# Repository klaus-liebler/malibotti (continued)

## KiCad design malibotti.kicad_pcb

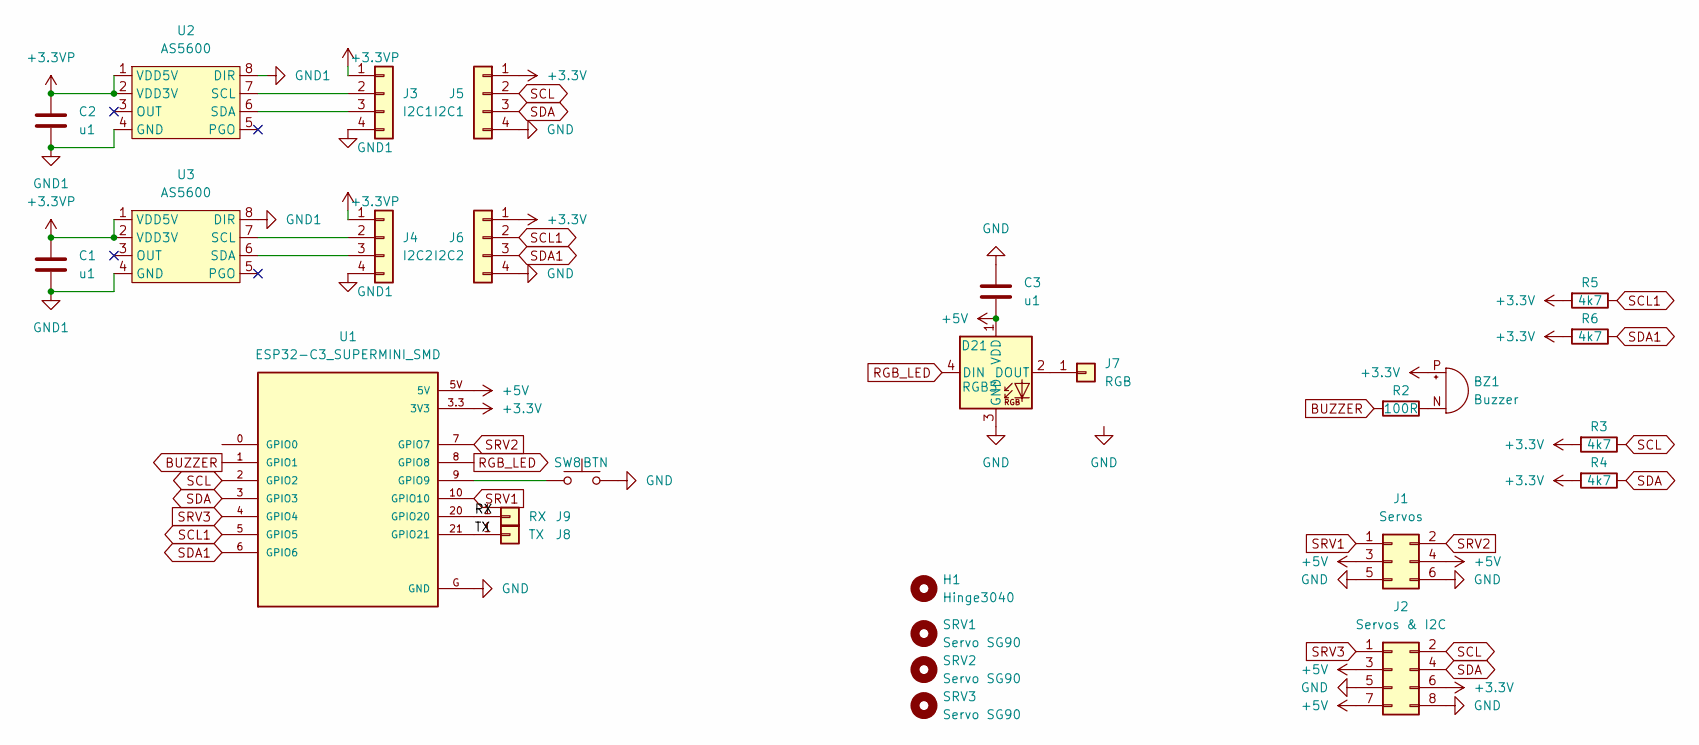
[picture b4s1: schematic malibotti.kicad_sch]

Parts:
BZ1: Buzzer; XDCR_CMT-7525-80-SMT-TR_handsolder
C1, C2, C3: u1; C_1206_3216Metric_Pad1.33x1.80mm_HandSolder
D21: RGB3; SK6812MINI-E_REV; MPN SK6812MINI-EA
H1: Hinge3040; Hinge_3040
J1: Servos; PinHeader_2x03_P2.54mm_Vertical_SMD
J2: Servos & I2C; PinHeader_2x04_P2.54mm_Vertical_SMD
J3: I2C1; PinHeader_1x04_P2.54mm_Vertical
J4: I2C2; PinHeader_1x04_P2.54mm_Vertical
J5: I2C1; PinSocket_1x04_P2.54mm_Vertical
J6: I2C2; PinSocket_1x04_P2.54mm_Vertical
J7: RGB; TestPoint_Pad_1.5x1.5mm
J8: TX; TestPoint_Pad_1.5x1.5mm
J9: RX; TestPoint_Pad_1.5x1.5mm
R2: 100R; R_1206_3216Metric_Pad1.30x1.75mm_HandSolder
R3, R4, R5, R6: 4k7; R_1206_3216Metric_Pad1.30x1.75mm_HandSolder
SRV1, SRV2: Servo SG90; SG90_PCB
SRV3: Servo SG90; SG90_vertical_PCB
SW8: BTN; SW_Push_1P1T_NO_6x6mm_H6.5mm_Reverse; MPN TS-1095E-A6B3-D2
U1: ESP32-C3_SUPERMINI_SMD; MODULE_ESP32-C3_SUPERMINI
U2, U3: AS5600; SOIC-8_3.9x4.9mm_P1.27mm_handsolder

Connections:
+3.3V: BZ1.P (+), J2.6, J5.1, J6.1, R3.2, R4.2, R5.2, R6.2, U1.3.3 (3V3)
+3.3VP: C1.1, C2.1, J3.1, J4.1, U2.1 (VDD5V), U2.2 (VDD3V), U3.1 (VDD5V), U3.2 (VDD3V)
+5V: C3.1, D21.1 (VDD), J1.3, J1.4, J2.3, J2.7, U1.5V
/RX: J9.1, U1.20 (GPIO20)
/TX: J8.1, U1.21 (GPIO21)
BUZZER: R2.2, U1.1 (GPIO1)
GND: C3.2, D21.3 (GND), J1.5, J1.6, J2.5, J2.8, J5.4, J6.4, SW8.2, U1.G (GND)
GND1: C1.2, C2.2, J3.4, J4.4, U2.4 (GND), U2.8 (DIR), U3.4 (GND), U3.8 (DIR)
unnamed: BZ1.N (-), R2.1
unnamed: D21.2 (DOUT), J7.1
unnamed: J3.2, U2.7 (SCL)
unnamed: J3.3, U2.6 (SDA)
unnamed: J4.2, U3.7 (SCL)
unnamed: J4.3, U3.6 (SDA)
unnamed: SW8.1, U1.9 (GPIO9)
RGB_LED: D21.4 (DIN), U1.8 (GPIO8)
SCL: J2.2, J5.2, R3.1, U1.2 (GPIO2)
SCL1: J6.2, R5.1, U1.5 (GPIO5)
SDA: J2.4, J5.3, R4.1, U1.3 (GPIO3)
SDA1: J6.3, R6.1, U1.6 (GPIO6)
SRV1: J1.1, U1.10 (GPIO10)
SRV2: J1.2, U1.7 (GPIO7)
SRV3: J2.1, U1.4 (GPIO4)

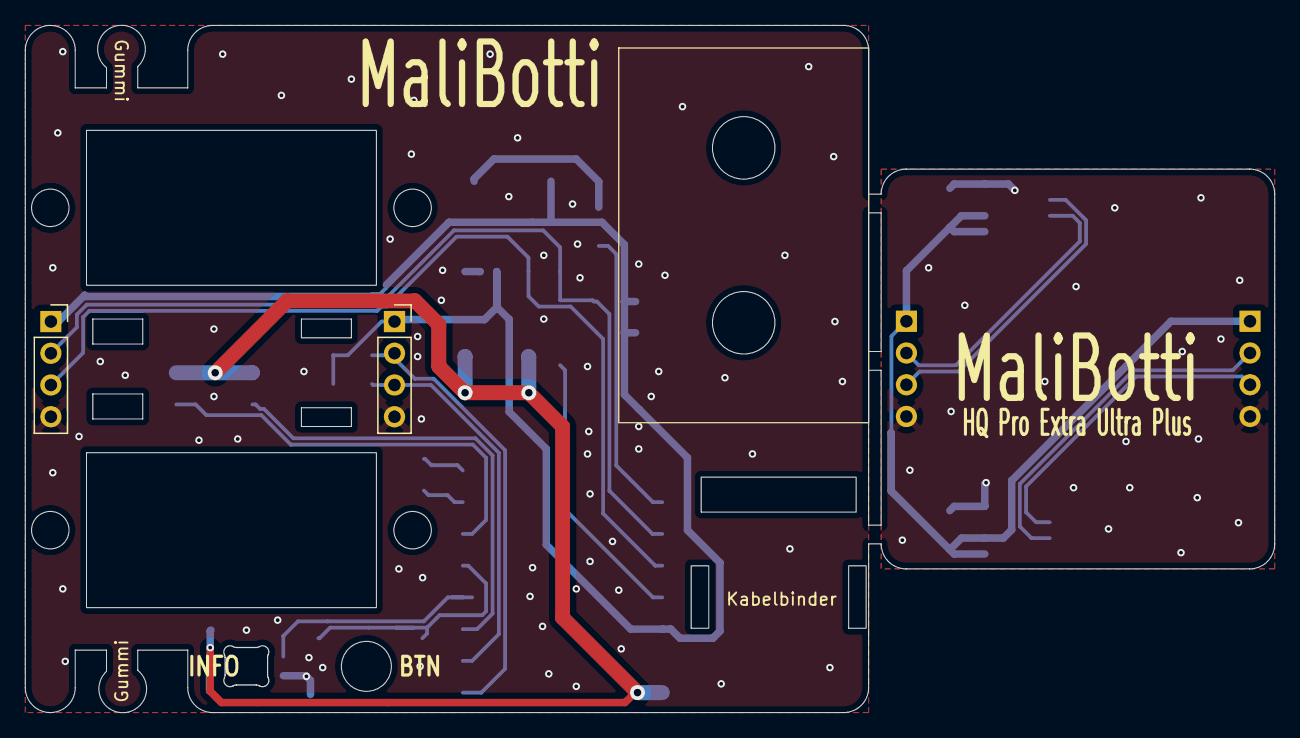
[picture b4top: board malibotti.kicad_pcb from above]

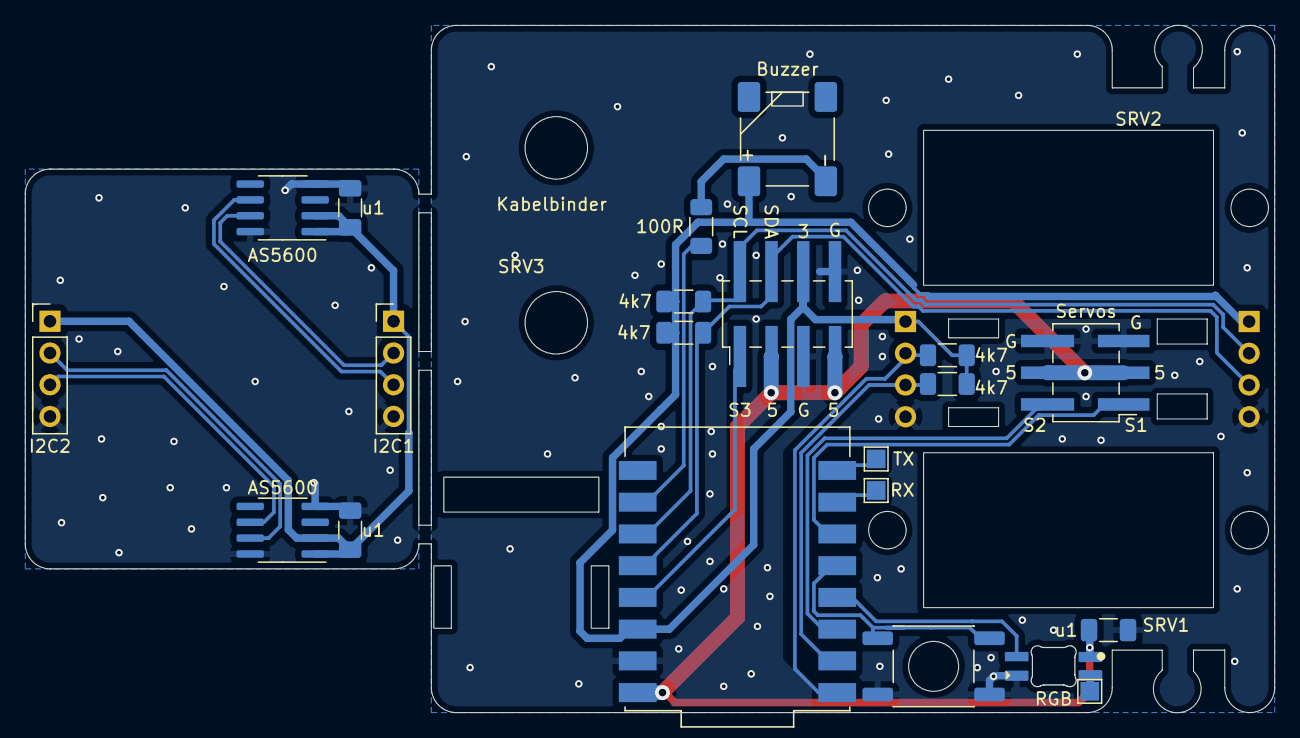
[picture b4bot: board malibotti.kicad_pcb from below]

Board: 2 copper layers, 100.0 x 55.0 mm, 27 parts (21 on the bottom side), 23 nets.

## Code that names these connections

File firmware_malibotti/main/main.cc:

#include <stdlib.h>
#include <stdio.h>
#include <string.h>
#include <errno.h>
#include <stdarg.h>
#include <fcntl.h>
#include <array>
#include <sys/types.h>
#include <unistd.h>

#include "sdkconfig.h"
#include "esp_log.h"
#include "esp_mac.h"
#include "esp_system.h"
#include "esp_vfs.h"
#include "freertos/FreeRTOS.h"
#include "freertos/task.h"
#include "rgbled.hh"
#include "esp_rom_gpio.h"

#include "hal/gpio_ll.h"

#include "driver/gpio.h"
#include "driver/uart.h"

#include "buzzer.hh"
#include "listener/echo_message_processor.hh"
#include "listener/rgb_message_processor.hh"
#include "listener/servo_message_processor.hh"
#include "listener/stepper_message_processor.hh"
#include "stepper_unipolar.hh"
#include "usb.hh"

constexpr const char MONITOR_LOG_TAG[] = "monitor";

namespace P
{
  constexpr gpio_num_t BUTTON{GPIO_NUM_0};
  constexpr gpio_num_t LIMIT_RIGHT{GPIO_NUM_6};
  constexpr gpio_num_t LIMIT_LEFT{GPIO_NUM_7};
  constexpr gpio_num_t RGB_LED{GPIO_NUM_11};
  constexpr gpio_num_t STEPPER1_PH1{GPIO_NUM_21};
  constexpr gpio_num_t STEPPER1_PH2{GPIO_NUM_47};
  constexpr gpio_num_t STEPPER1_PH3{GPIO_NUM_34};
  constexpr gpio_num_t STEPPER1_PH4{GPIO_NUM_35};
  constexpr gpio_num_t STEPPER2_PH1{GPIO_NUM_36};
  constexpr gpio_num_t STEPPER2_PH2{GPIO_NUM_48};
  constexpr gpio_num_t STEPPER2_PH3{GPIO_NUM_33};
  constexpr gpio_num_t STEPPER2_PH4{GPIO_NUM_26};
  constexpr gpio_num_t SERVO{GPIO_NUM_37};
  constexpr gpio_num_t BUZZER{GPIO_NUM_38};
  constexpr gpio_num_t SDA{GPIO_NUM_39};
  constexpr gpio_num_t SCL{GPIO_NUM_40};
}

namespace stepper_settings
{
  constexpr uint16_t STEPS_PER_REV = 2048;
  constexpr uint32_t MAX_RPM = 12;
  constexpr TickType_t TURN_PAUSE = pdMS_TO_TICKS(500);
  constexpr bool USE_HALF_STEP = false;
}

constexpr TickType_t CDC_LOG_WRITE_TIMEOUT_TICKS = pdMS_TO_TICKS(20);

/* Blink pattern
 * - 250 ms  : device not mounted
 * - 1000 ms : device mounted
 * - 2500 ms : device is suspended
 */
RGBLED::BlinkPattern NOT_MOUNTED(CRGB::Red, 250, CRGB::Black, 250);
RGBLED::BlinkPattern MOUNTED(CRGB::Green, 1000, CRGB::Black, 1000);
RGBLED::BlinkPattern SUSPENDED(CRGB::Blue, 250, CRGB::Black, 2250);
RGBLED::MultipleFlashesPattern USB_INIT_FAILED(CRGB::Red, 2);

RGBLED::M<1, RGBLED::DeviceType::WS2812> s_board_led;
BUZZER::M s_buzzer;
ISendBackInterface *s_sendBack;
int (*s_previous_log_vprintf)(const char *, va_list) = nullptr;

using Stepper1 = StepperUnipolar<P::STEPPER1_PH1,
                                 P::STEPPER1_PH3,
                                 P::STEPPER1_PH2,
                                 P::STEPPER1_PH4,
                                 stepper_settings::STEPS_PER_REV,
                                 false,
                                 stepper_settings::USE_HALF_STEP>;

using Stepper2 = StepperUnipolar<P::STEPPER2_PH1,
                                 P::STEPPER2_PH3,
                                 P::STEPPER2_PH2,
                                 P::STEPPER2_PH4,
                                 stepper_settings::STEPS_PER_REV,
                                 false,
                                 stepper_settings::USE_HALF_STEP>;

static Stepper1 s_stepper1;
static Stepper2 s_stepper2;

static std::array<IMessageProcessor *, 5> message_processors{
  new listener::EchoMessageProcessor(),
  new listener::RGBMessageProcessor(s_board_led),
  new listener::ServoMessageProcessor(P::SERVO),
  new listener::StepperMessageProcessor<0x0004>(s_stepper1),
  new listener::StepperMessageProcessor<0x0005>(s_stepper2)
};

static void process_vendor_binary_message(const uint8_t msg[usb_bridge::kBinaryMsgSize])
{
  uint16_t const name_space = static_cast<uint16_t>(msg[0] | (static_cast<uint16_t>(msg[1]) << 8));
  uint16_t const message_id = static_cast<uint16_t>(msg[2] | (static_cast<uint16_t>(msg[3]) << 8));
  uint8_t const *payload = msg + 4;

  IMessageProcessor *message_listener = nullptr;
  for (auto *processor : message_processors)
  {
    if (processor != nullptr && processor->GetNamespace() == name_space)
    {
      message_listener = processor;
      break;
    }
  }

  if (message_listener == nullptr)
  {
    return;
  }

  message_listener->Handle(*s_sendBack, message_id, payload);
}

static void processing_task(void *context)
{
  (void)context;

  while (true)
  {
    s_board_led.Refresh();
    s_buzzer.Loop();
    uint32_t const now_ms = static_cast<uint32_t>(esp_timer_get_time() / 1000);
    for (auto *processor : message_processors)
    {
      if (processor != nullptr)
      {
        processor->Loop(*s_sendBack, now_ms);
      }
    }
    vTaskDelay(pdMS_TO_TICKS(10));
  }
}

extern "C" void app_main(void)
{
  s_sendBack = new usb_bridge::VendorSendBack();
  usb_bridge::SetVendorMessageHandler(process_vendor_binary_message);

  s_stepper1.Init();
  s_stepper2.Init();

  s_board_led.Begin(SPI2_HOST, P::RGB_LED);
  s_buzzer.Begin(P::BUZZER);
  s_buzzer.PlaySong(1);

  for (auto *processor : message_processors)
  {
    if (processor != nullptr)
    {
      processor->Setup(*s_sendBack, 0);
    }
  }

  esp_rom_gpio_pad_select_gpio(P::BUTTON);
  gpio_set_direction(P::BUTTON, GPIO_MODE_INPUT);
  gpio_set_pull_mode(P::BUTTON, GPIO_PULLUP_ONLY);

  ESP_ERROR_CHECK(usb_bridge::Init());

  xTaskCreate(processing_task, "processing", 4096, nullptr, tskIDLE_PRIORITY + 2, nullptr);

  while (true)
  {
    ESP_LOGI(
        MONITOR_LOG_TAG,
        "mntd=%d sspnd=%d cdc_cnctd=%d cdc_rx=%u cdc_tx_free=%u btn=%d heap=%lu",
        tud_mounted() ? 1 : 0,
        tud_suspended() ? 1 : 0,
        tud_cdc_connected() ? 1 : 0,
        static_cast<unsigned>(tud_cdc_available()),
        static_cast<unsigned>(tud_cdc_write_available()),
        !gpio_get_level(P::BUTTON),
        static_cast<unsigned long>(esp_get_free_heap_size()));
    vTaskDelay(pdMS_TO_TICKS(3000));
  }
}

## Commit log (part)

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2025-10-04 Improvements
2025-10-12 Malibotti as ordered @ JLCPCB
2026-02-03 moved files
2026-02-10 PCB v2
2026-02-24 Added serial port
2026-02-25 Various
2026-03-22 Malibotti Stepper + renaming
2026-04-01 Malibotti WIP
2026-04-08 Malibotti Stepper Release Candidate
2026-04-13 Limit Switch
2026-04-22 Minor improvements
2026-05-11 update to Kicad 10
2026-05-11 Malibotti stepper as ordered @ JLCPCB
